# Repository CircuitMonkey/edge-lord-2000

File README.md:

# edge-lord-2000
ESP32 based vibrator controller, four channel, OLED screen

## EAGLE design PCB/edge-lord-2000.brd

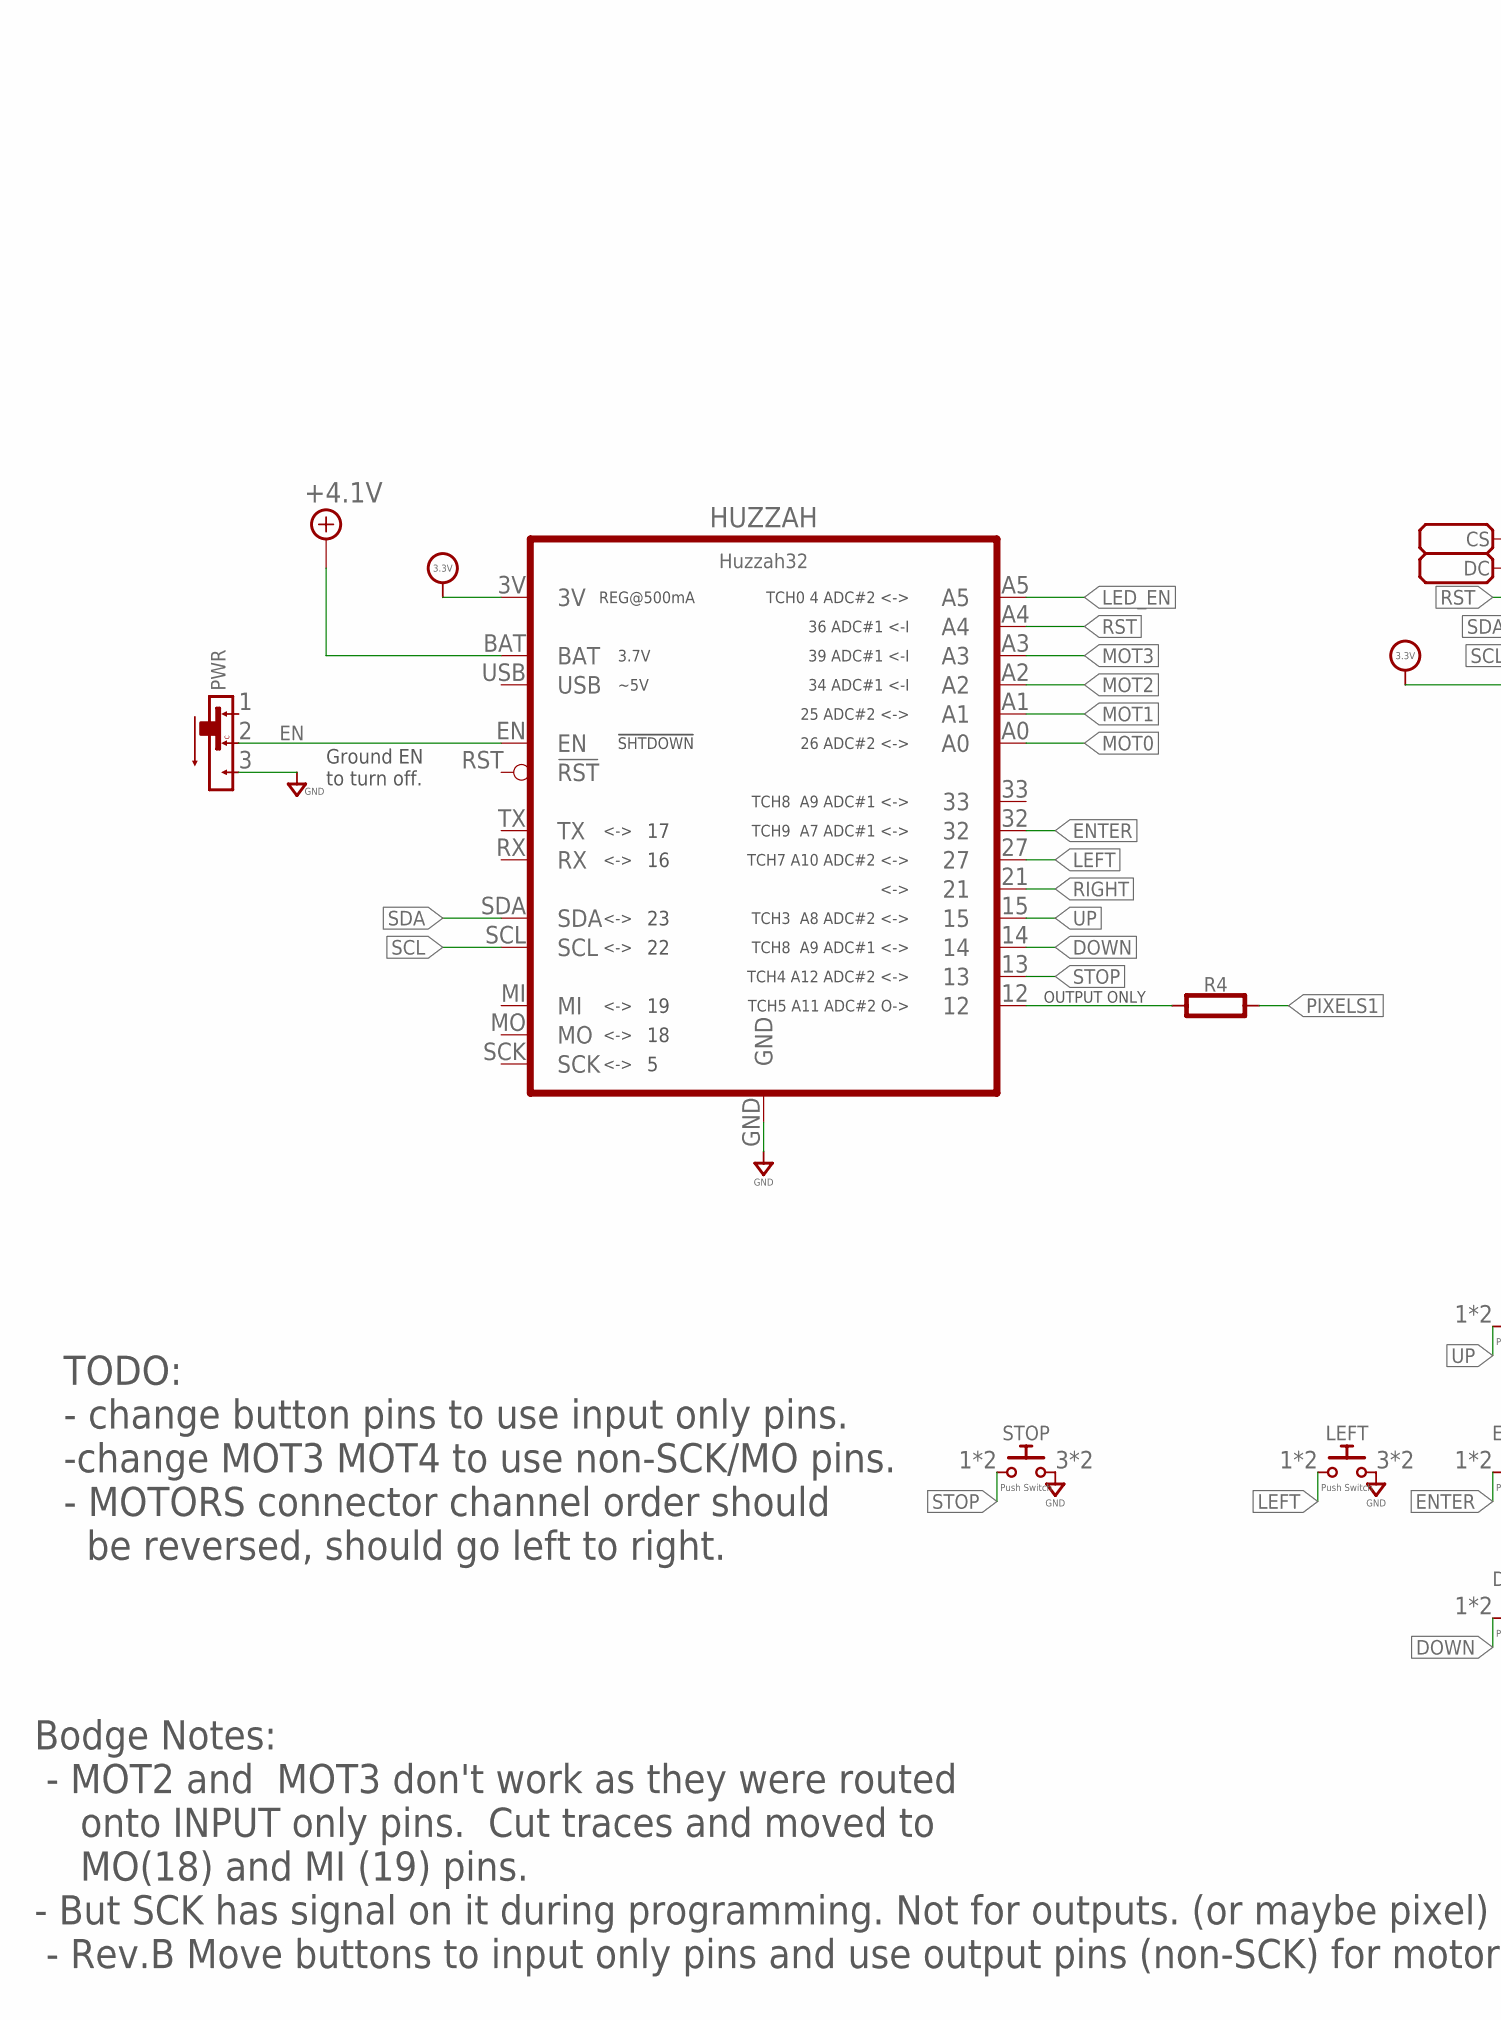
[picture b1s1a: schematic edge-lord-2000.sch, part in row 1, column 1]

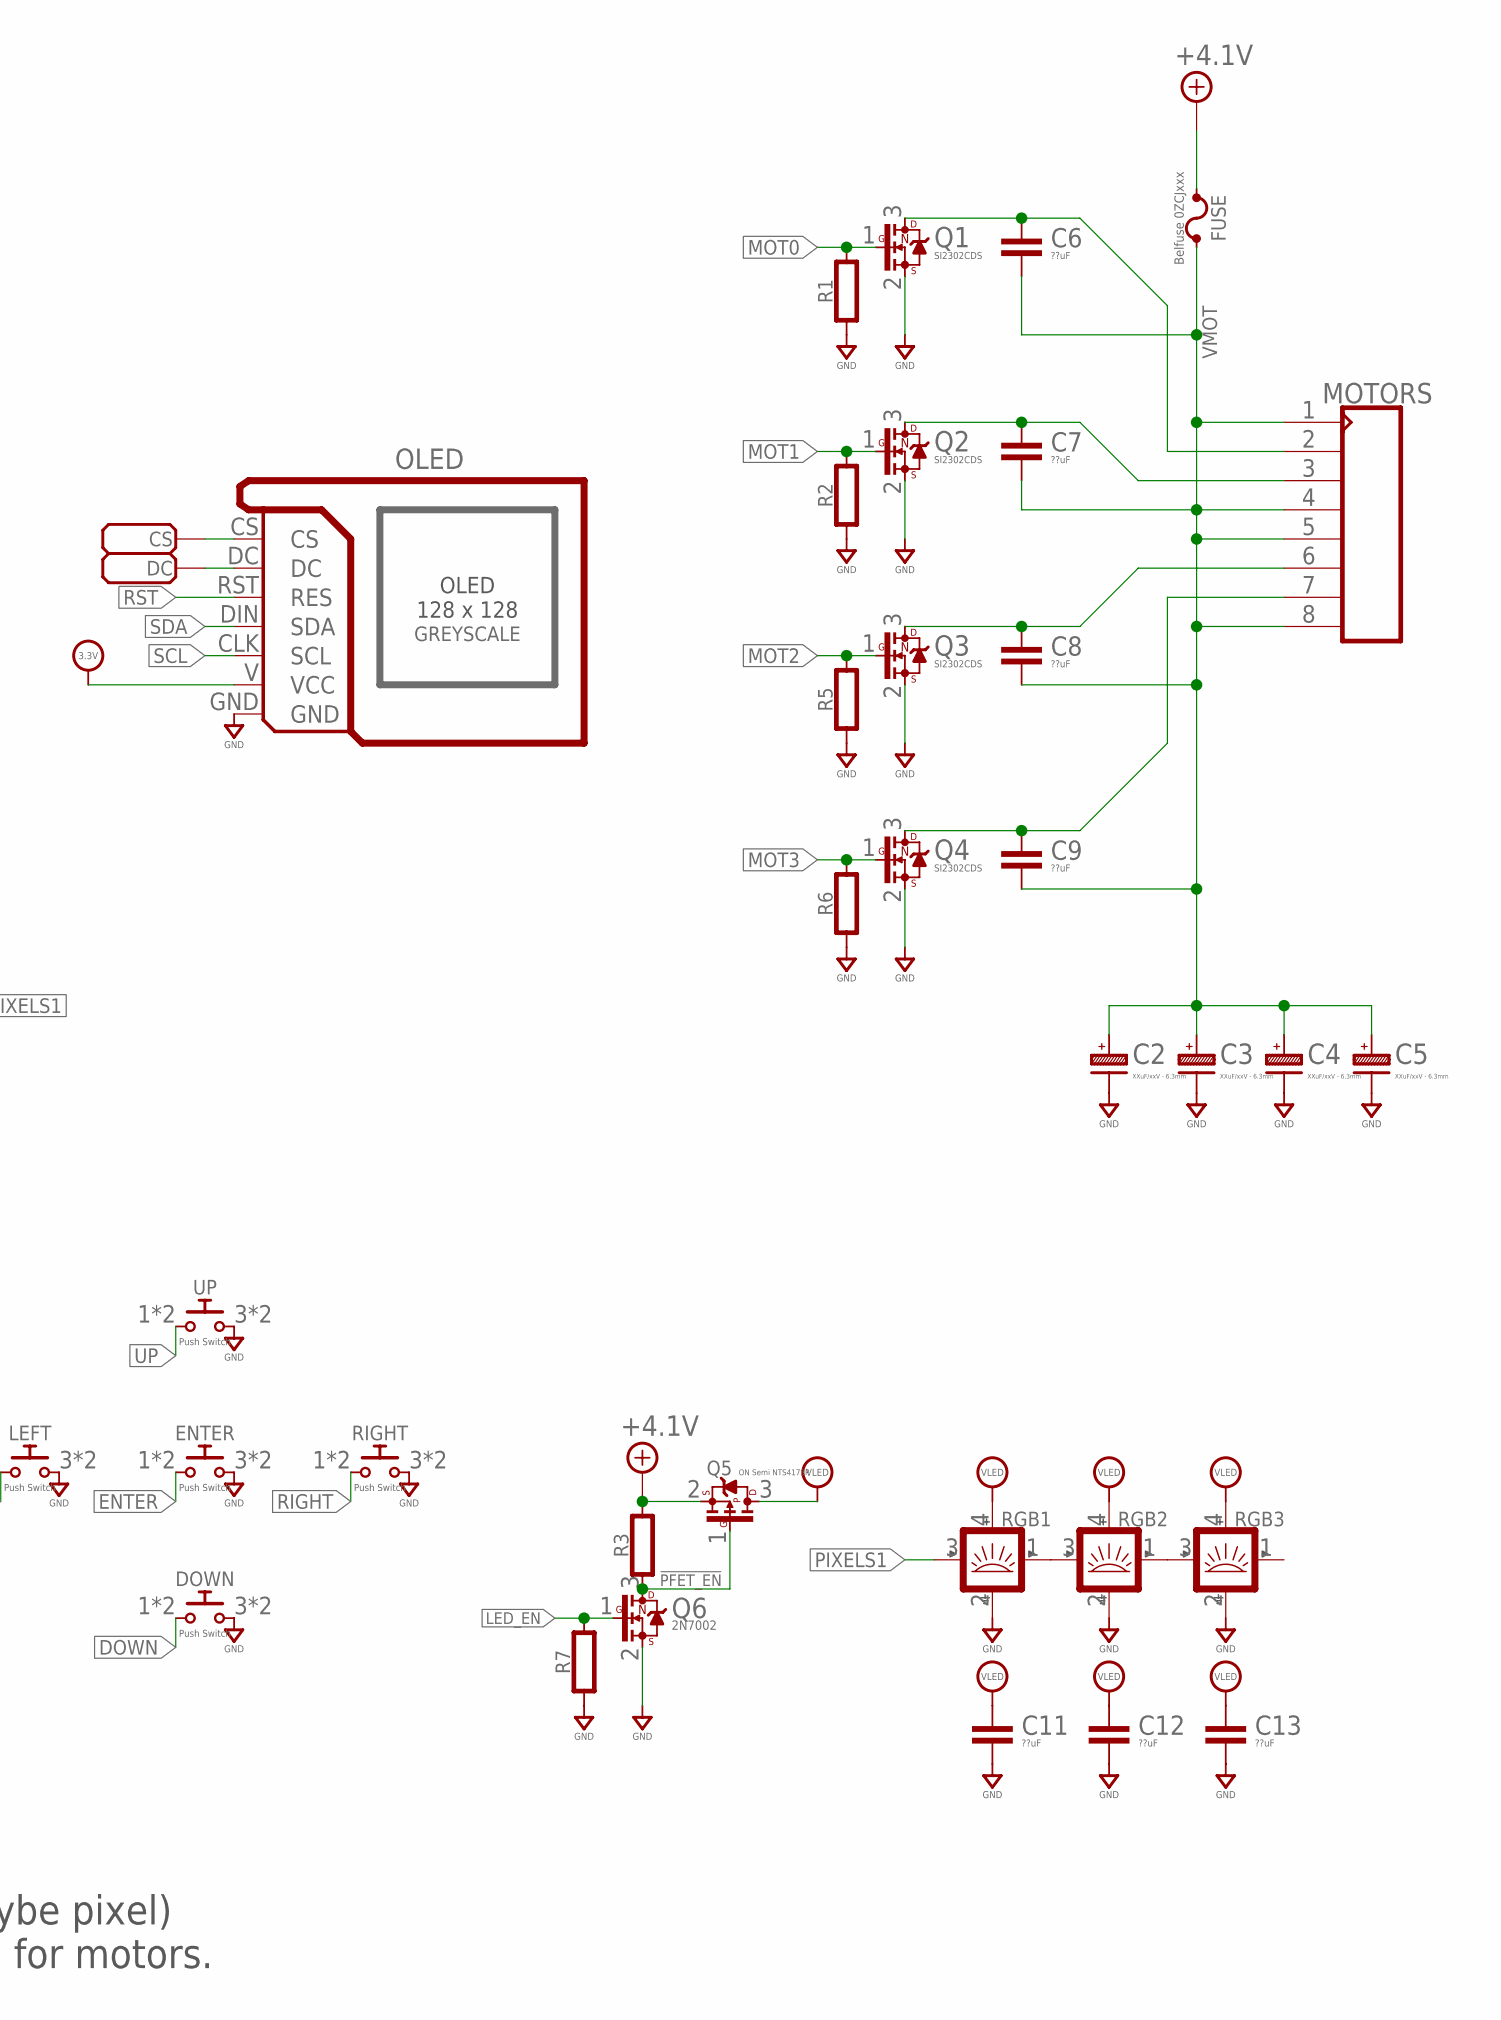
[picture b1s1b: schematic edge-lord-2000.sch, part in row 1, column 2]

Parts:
C2, C3, C4, C5: XXuF/xxV - 6.3mm; CAP_ALUM_SMT_6.3
C6, C7, C8, C9, C11, C12, C13: ??uF; 0603-CAP
CS: PADSMD-070X070; SMD-070MIL
DC: PADSMD-070X070; SMD-070MIL
DOWN: Push Switch; B3SN
ENTER: Push Switch; B3SN
FUSE: Belfuse 0ZCJxxx; BELFUSE-1206
HUZZAH: Huzzah32; ADAFRUIT_HUZZAH32
LEFT: Push Switch; B3SN
MOTORS: CON_08X1-RA-THD; MA08X1-RA-THD
OLED: GREYSCALE; SSD1327-THD-MODULE
PWR: SLIDE-SPDTJS102011JCQN; CK_JS102011JCQN
Q1, Q2, Q3, Q4: SI2302CDS; SOT-23
Q5: ON Semi NTS4173P; SOT-323
Q6: 2N7002; SOT-23
R1, R2, R5, R6, R7: 100K; 0603-RES
R3: 20K; 0603-RES
R4: 330; 0603-RES
RGB1, RGB2, RGB3: SMART_LED3535; SMD_3535
RIGHT: Push Switch; B3SN
STOP: Push Switch; B3SN
UP: Push Switch; B3SN

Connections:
!PFET_EN: Q5.1 (G), Q6.3 (D), R3.1
+3.3V: HUZZAH.3V, OLED.V (VCC)
+4.1V: FUSE.1, HUZZAH.BAT, Q5.2 (S), R3.2
DOWN: DOWN.1, DOWN.2 (1), HUZZAH.14
EN: HUZZAH.EN, PWR.2
ENTER: ENTER.1, ENTER.2 (1), HUZZAH.32
GND: C2.- (N), C3.- (N), C4.- (N), C5.- (N), C11.2, C12.2, C13.2, DOWN.3 (2), DOWN.4 (2), ENTER.3 (2), ENTER.4 (2), HUZZAH.GND, LEFT.3 (2), LEFT.4 (2), OLED.GND, PWR.3, Q1.2 (S), Q2.2 (S), Q3.2 (S), Q4.2 (S), Q6.2 (S), R1.1, R2.1, R5.1, R6.1, R7.1, RGB1.2 (GND), RGB2.2 (GND), RGB3.2 (GND), RIGHT.3 (2), RIGHT.4 (2), STOP.3 (2), STOP.4 (2), UP.3 (2), UP.4 (2)
LED_EN: HUZZAH.A5, Q6.1 (G), R7.2
LEFT: HUZZAH.27, LEFT.1, LEFT.2 (1)
MOT0: HUZZAH.A0, Q1.1 (G), R1.2
MOT1: HUZZAH.A1, Q2.1 (G), R2.2
MOT2: HUZZAH.A2, Q3.1 (G), R5.2
MOT3: HUZZAH.A3, Q4.1 (G), R6.2
unnamed: C6.1, MOTORS.2, Q1.3 (D)
unnamed: C8.1, MOTORS.6, Q3.3 (D)
unnamed: C7.1, MOTORS.3, Q2.3 (D)
unnamed: CS.1, OLED.CS
unnamed: DC.1, OLED.DC
unnamed: RGB1.1 (OUT), RGB2.3 (IN)
unnamed: RGB2.1 (OUT), RGB3.3 (IN)
unnamed: HUZZAH.12, R4.1
unnamed: C9.1, MOTORS.7, Q4.3 (D)
PIXELS1: R4.2, RGB1.3 (IN)
RIGHT: HUZZAH.21, RIGHT.1, RIGHT.2 (1)
RST: HUZZAH.A4, OLED.RST (RES)
SCL: HUZZAH.SCL, OLED.CLK (SCL)
SDA: HUZZAH.SDA, OLED.DIN (SDA)
STOP: HUZZAH.13, STOP.1, STOP.2 (1)
UP: HUZZAH.15, UP.1, UP.2 (1)
VLED: C11.1, C12.1, C13.1, Q5.3 (D), RGB1.4 (VDD), RGB2.4 (VDD), RGB3.4 (VDD)
VMOT: C2.+, C3.+, C4.+, C5.+, C6.2, C7.2, C8.2, C9.2, FUSE.2, MOTORS.1, MOTORS.4, MOTORS.5, MOTORS.8

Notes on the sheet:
OUTPUT ONLY
TODO: - change button pins to use input only pins. -change MOT3 MOT4 to use non-SCK/MO pins. - MOTORS connector channel order should be reversed, should go left to right.
Ground EN to turn off.
Bodge Notes: - MOT2 and MOT3 don't work as they were routed onto INPUT only pins. Cut traces and moved to MO(18) and MI (19) pins. - But SCK has signal on it during programming. Not for outputs. (or maybe pixel) - Rev.B Move buttons to input only pins and use output pins (non-SCK) for motors.

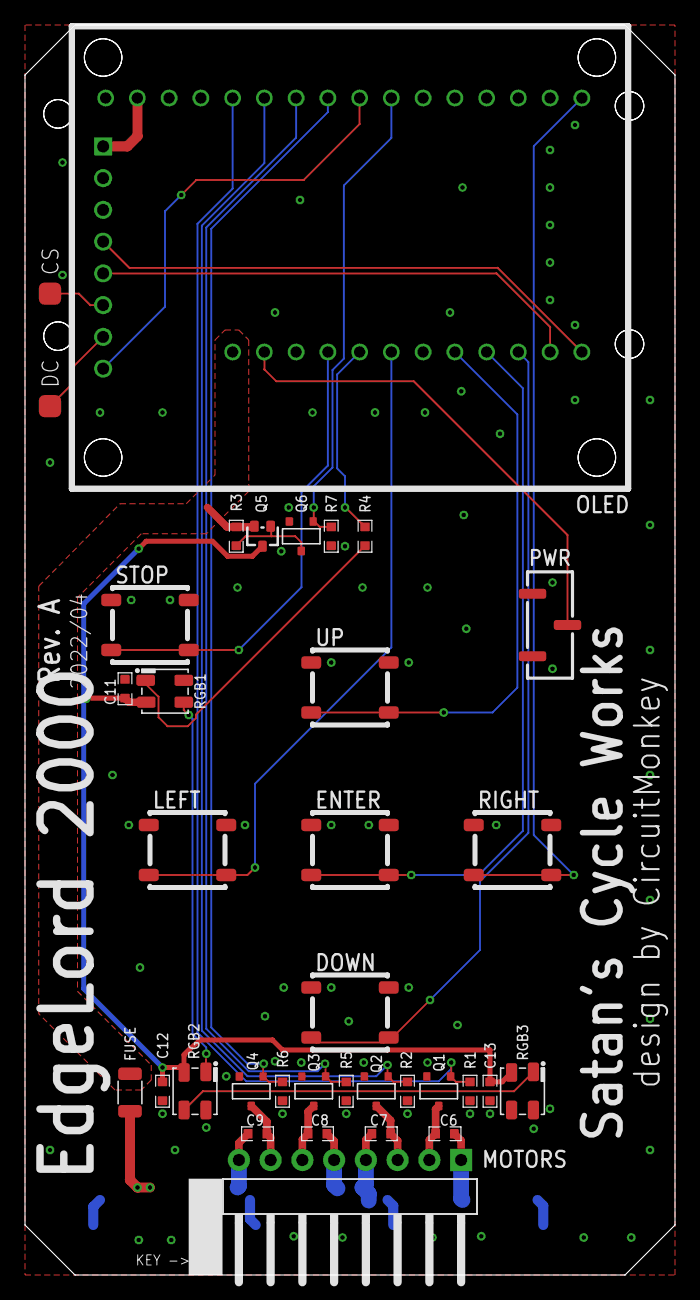
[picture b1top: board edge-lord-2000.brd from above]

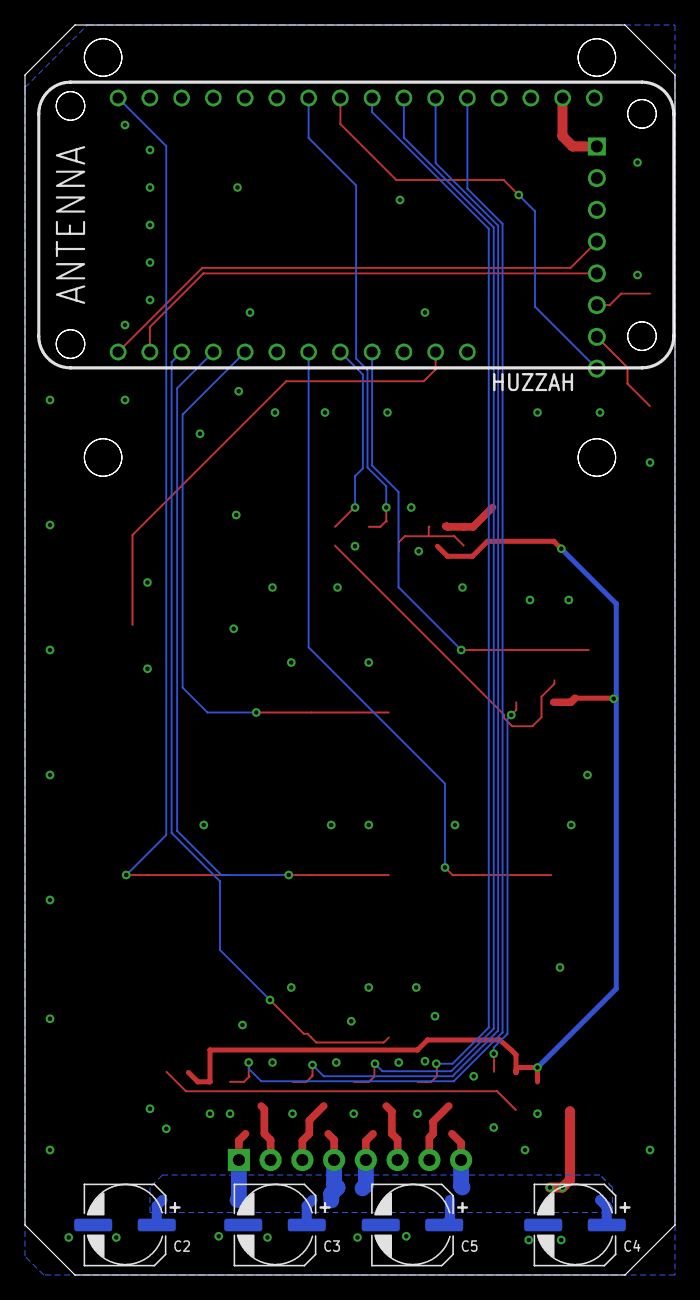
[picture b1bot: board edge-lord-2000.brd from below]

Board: 2 copper layers, 52.0 x 100.0 mm, 40 parts (5 on the bottom side), 31 nets.

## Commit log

2022-04-19 Rev. A (final?)
2022-04-20 PWR switch was backward. Updated 3D model for fusion.
2022-05-05 PCB Rev.A tweaks.
2022-05-05 Individual tests for PCB function.
2022-05-11 Bodge Notes added to schematic
2022-05-11 Check point main code.
    Two modes working. Left-right mode needs tuning. No other modes work yet.
2022-05-16 main code working with three modes.
    Manual, Cycle and Left-Right working.
2022-05-16 Clean up code. Add two modes.
    Cleaned up use of defines for ANIM_STEPS. Added UpDown and Cross modes. Cleaned out commented old code.
2022-05-17 Stop animation timer if paused.
2022-05-17 Add Random Mode
2022-05-17 Update slider settings for most modes.
2022-05-17 More notes in PCB. Update Huzzah symbol.
2022-05-31 Fix issue where N_SLIDERS was not properly referenced.
2022-05-31 Add Hammer Mode. More motor speed. Add Debounce.
